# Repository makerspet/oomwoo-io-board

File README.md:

<div align="center">

# OOMWOO I/O Board

*Open-source robot vacuum you build yourself.*

Raspberry Pi CM4/CM5 socket · STM32G473 MCU · Motor drivers · Sensors · 2x MIPI cameras · 4S charging · KiCad

</div>

Part of [OOMWOO open-source robot vacuum](https://github.com/makerspet/oomwoo) project.

Get [MCU firmware](https://github.com/makerspet/oomwoo-io-firmware/).

## Architecture notes

Consumer vacuums typically split compute into CPU and MCU. The MCU ([real examples](https://robotinfo.dev/)) controls
- all motors - driving wheels, suction fan, side brushes, mop motors, mop lift servos, pump and so on
- all sensors except below - IR cliff, IR side proximity, IR docking, wheel drop, bumper (IR or micro-switches), motor encoders, ultrasonic carpet sensor
- all push buttons
- 2D LiDAR motor RPM
- power - battery charging, motors power on/off
- all safety sensors - overcurrent for all motors (cheap vacuums ignore overcurrent sensing)

I/O board also provides audio encoders/decoders, amp, speaker (connector), mics (if any).

CPU receives
- 2D LiDAR data over serial port
- IMU (sometimes IMU gets forwarded via MCU) over SPI/I2C
- cameras (2x MIPI for visual obstacle avoidance)

MCU (and CPU) are usually always active. This allows the user to start cleaning at any time (especially via app remotely). Exceptions:
- no power (battery dead and no dock power)
- user explicitly shut down the vacuum by long-pressing the power button

The MCU's overarching constraint is to ensure robot safety. This is necessary to pass CE mark tests. Here is how MCU ensures safety:
- MCU firmware uses FreeRTOS or similar, static memory allocation, watchdog, guaranteed reaction time
- MCU acts as watchdog for CPU, resets CPU if CPU becomes unresponsive
- MCU connects to CPU over serial using a custom serial protocol ([concrete example](https://github.com/codetiger/VacuumRobot)). No micro-ROS to reduce dependencies, prevent bugs from updated 3rd party libraries slipping into safety-critical MCU firmware.
- MCU shuts down some (or all) motors when MCU detects overcurrent (brush stuck)
- MCU shuts down all motors (including power to all motors) when CPU becomes unresponsive (to prevent CPU sending garbage commands to MCU)
- MCU monitors battery charging, shuts it down when needed (battery too hot)
- MCU stops driving wheel motors when bumper sensors activate
- MCU tests motors, sensors
- MCU does not depend on CPU
- MCU toggles watchdog GPIO; otherwise an external-to-MCU circuit shuts down motor power

Consumer vacuums place CPU and MCU on the same PCB board. Since OOMWOO has to be hackable, it seems best to separate I/O from the compute. Therefore, this I/O board needs to have
- MCU and programming header
  - likely STM32G070RBT6 because it has 56 GPIOs, 16 ADC channels, costs $1 at JLCPCB, has LQFP package for easy PCBA - a rare combination
  - see tentative [I/O board spec](https://github.com/makerspet/oomwoo-io-board/blob/main/docs/SPEC.md)
- all vacuum motor drivers (with connectors), driven by the MCU
  - cliff, side proximity, docking, bumper, carpet, water tank full/empty, dust bin present, motor overcurrent, motor encoders
- MCU connected to all sensors (except those handled by CPU like LiDAR serial, MIPI cameras I/O, IMU); sensor connectors
- control circuit for 2D LiDAR's motor (controlled by MCU)
- battery charging, power management (motors power on/off, charging on/off, power shut down), power for CPU compute module (see below)
- push buttons (home, power, etc.) and UI LEDs
- dock connector (dock power, sense dock present)
- USB power for charging; USB for serial shell, etc.
- audio encoder/decoder, audio amp, mics (if any)
- SD card for hacking, cheap large storage
- connect IMU FSYNC to MCU to synchronize MCU timestamps with IMU data streaming to CPU

Consumer vacuums usually don't have a CPU fan/heatsink because the vacuum's suction fan can (indirectly) cool the CPU/MCU PCB. Therefore, no CPU fan on this I/O board.

As far as compute - currently it seems best to use a Raspberry Pi CM4/CM5 compute module. Why?
- CM4/CM5 modules cost a bit less than a full Raspberry Pi 4/5
- CM4/CM5 have lower profile/height vs a full Raspberry Pi 4/5, important to keep vacuum cleaner slim
- there are plenty of 3rd party compute modules pin-compatible with CM4/CM5, making the compute swappable, hackable
  - 3rd party compute modules with NPUs are especially interesting because we need NPU for real-time camera-based obstacle detection

Compute module headers should expose
- 2x MIPI camera I/O
- 1x serial for CPU-MCU comms
- 1x serial for CPU-LiDAR comms
- 1x SPI (or I2C) for CPU-IMU comms
- audio (digital?) I/O
- power from I/O board to CM
- a few TBD GPIOs
  - MCU GPIO to reset CPU

This board should be designed using an open-source PCB tool (KiCad seems like a good choice).

## License

[Apache License 2.0](LICENSE).

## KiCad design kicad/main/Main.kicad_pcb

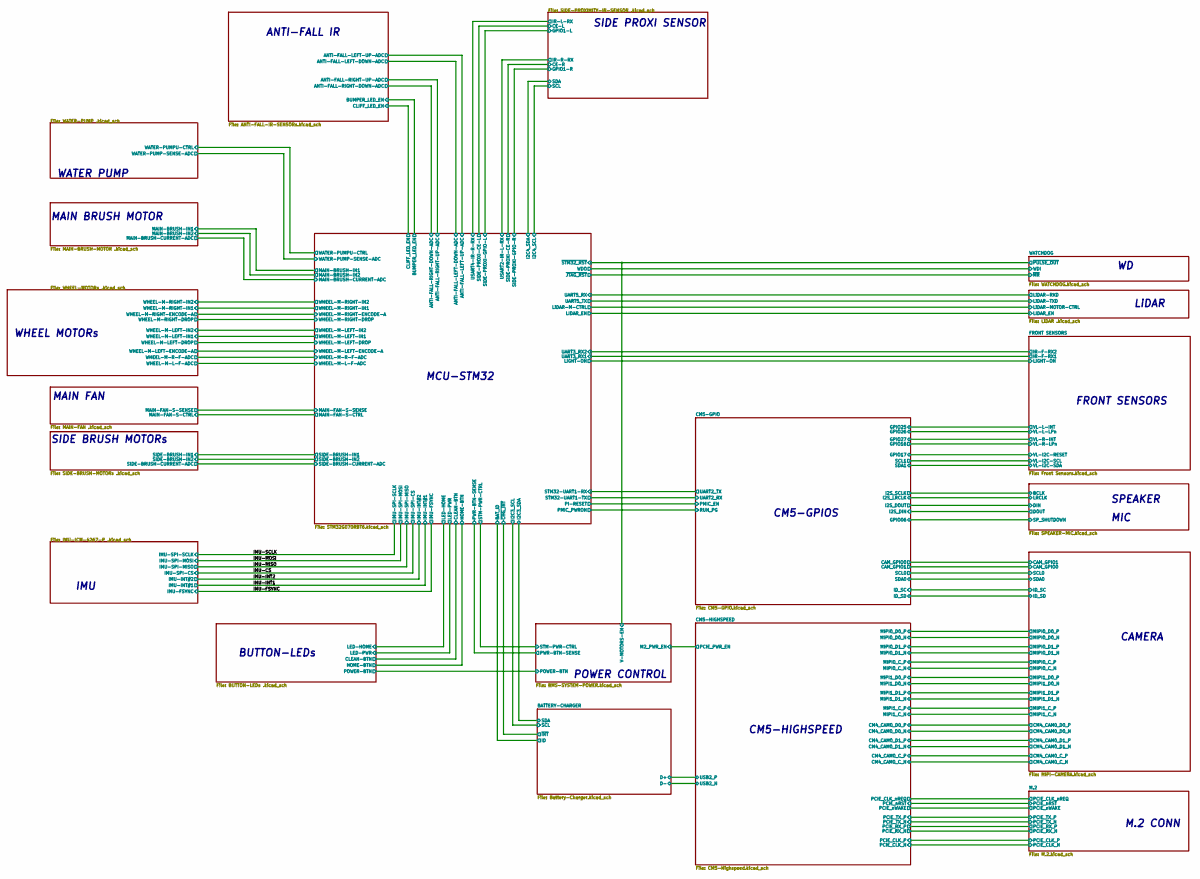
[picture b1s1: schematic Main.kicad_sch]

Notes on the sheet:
IMU
ANTI-FALL IR
WATER PUMP
FRONT SENSORS
M.2 CONN
CAMERA
MAIN FAN
BUTTON-LEDs
SIDE PROXI SENSOR
MCU-STM32
CM5-HIGHSPEED
SPEAKER
POWER CONTROL
WHEEL MOTORs
LiDAR
SIDE BRUSH MOTORs
MAIN BRUSH MOTOR
CM5-GPIOS
MIC

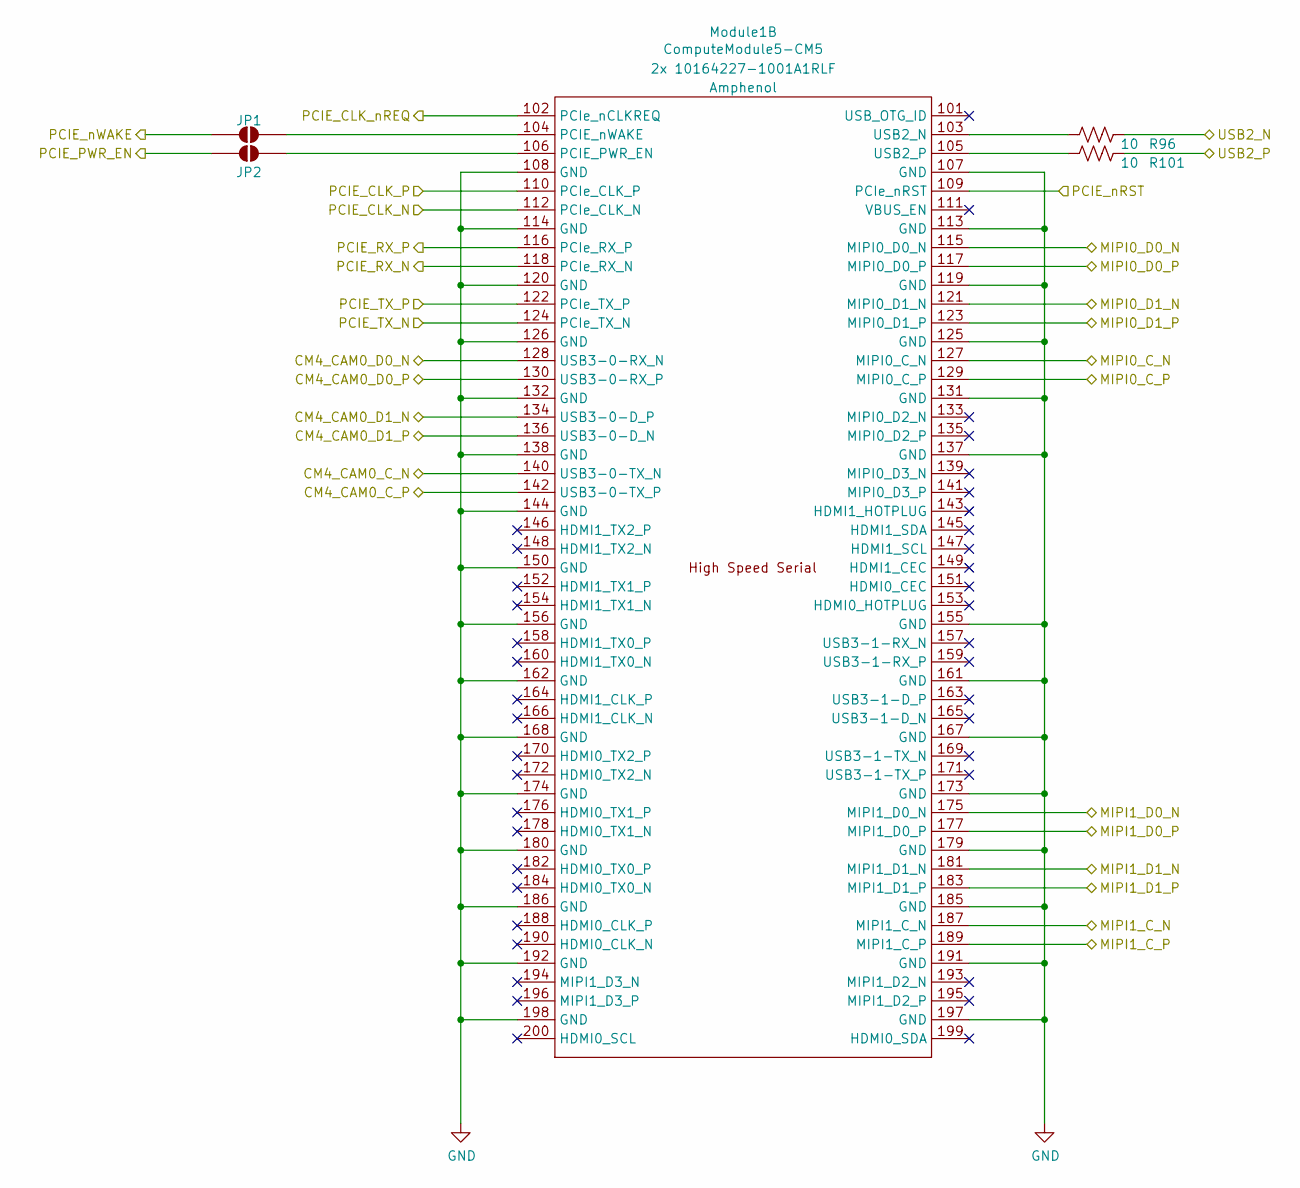
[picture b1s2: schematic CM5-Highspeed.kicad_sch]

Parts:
JP1, JP2: SolderJumper-2_P1.3mm_Open_RoundedPad1.0x1.5mm
Module1: ComputeModule5-CM5; Raspberry-Pi-5-Compute-Module; Part Description 100 Position Connector Receptacle, Cent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; LCSC 2X C6932320
R96, R101: 10; R_0603_1608Metric

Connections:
/BATTERY-CHARGER/D+: R101.2; also elsewhere on the board
/BATTERY-CHARGER/D-: R96.2; also elsewhere on the board
/CAMERA/CM4_CAM0_C_N: Module1.140 (USB3-0-TX_N); also elsewhere on the board
/CAMERA/CM4_CAM0_C_P: Module1.142 (USB3-0-TX_P); also elsewhere on the board
/CAMERA/CM4_CAM0_D0_N: Module1.128 (USB3-0-RX_N); also elsewhere on the board
/CAMERA/CM4_CAM0_D0_P: Module1.130 (USB3-0-RX_P); also elsewhere on the board
/CAMERA/CM4_CAM0_D1_N: Module1.134 (USB3-0-D_P); also elsewhere on the board
/CAMERA/CM4_CAM0_D1_P: Module1.136 (USB3-0-D_N); also elsewhere on the board
/CAMERA/MIPI0_C_N: Module1.127 (MIPI0_C_N); also elsewhere on the board
/CAMERA/MIPI0_C_P: Module1.129 (MIPI0_C_P); also elsewhere on the board
/CAMERA/MIPI0_D0_N: Module1.115 (MIPI0_D0_N); also elsewhere on the board
/CAMERA/MIPI0_D0_P: Module1.117 (MIPI0_D0_P); also elsewhere on the board
/CAMERA/MIPI0_D1_N: Module1.121 (MIPI0_D1_N); also elsewhere on the board
/CAMERA/MIPI0_D1_P: Module1.123 (MIPI0_D1_P); also elsewhere on the board
/CAMERA/MIPI1_C_N: Module1.187 (MIPI1_C_N); also elsewhere on the board
/CAMERA/MIPI1_C_P: Module1.189 (MIPI1_C_P); also elsewhere on the board
/CAMERA/MIPI1_D0_N: Module1.175 (MIPI1_D0_N); also elsewhere on the board
/CAMERA/MIPI1_D0_P: Module1.177 (MIPI1_D0_P); also elsewhere on the board
/CAMERA/MIPI1_D1_N: Module1.181 (MIPI1_D1_N); also elsewhere on the board
/CAMERA/MIPI1_D1_P: Module1.183 (MIPI1_D1_P); also elsewhere on the board
/CM5-HIGHSPEED/PCIE_CLK_N: Module1.112 (PCIe_CLK_N); also elsewhere on the board
/CM5-HIGHSPEED/PCIE_CLK_P: Module1.110 (PCIe_CLK_P); also elsewhere on the board
/CM5-HIGHSPEED/PCIE_CLK_nREQ: Module1.102 (PCIe_nCLKREQ); also elsewhere on the board
/CM5-HIGHSPEED/PCIE_PWR_EN: JP2.1 (A); also elsewhere on the board
/CM5-HIGHSPEED/PCIE_RX_N: Module1.118 (PCIe_RX_N); also elsewhere on the board
/CM5-HIGHSPEED/PCIE_RX_P: Module1.116 (PCIe_RX_P); also elsewhere on the board
/CM5-HIGHSPEED/PCIE_TX_N: Module1.124 (PCIe_TX_N); also elsewhere on the board
/CM5-HIGHSPEED/PCIE_TX_P: Module1.122 (PCIe_TX_P); also elsewhere on the board
/CM5-HIGHSPEED/PCIE_nRST: Module1.109 (PCIe_nRST); also elsewhere on the board
/CM5-HIGHSPEED/PCIE_nWAKE: JP1.1 (A); also elsewhere on the board
GND: Module1.107 (GND), Module1.108 (GND), Module1.113 (GND), Module1.114 (GND), Module1.119 (GND), Module1.120 (GND), Module1.125 (GND), Module1.126 (GND), Module1.131 (GND), Module1.132 (GND), Module1.137 (GND), Module1.138 (GND), Module1.144 (GND), Module1.150 (GND), Module1.155 (GND), Module1.156 (GND), Module1.161 (GND), Module1.162 (GND), Module1.167 (GND), Module1.168 (GND), Module1.173 (GND), Module1.174 (GND), Module1.179 (GND), Module1.180 (GND), Module1.185 (GND), Module1.186 (GND), Module1.191 (GND), Module1.192 (GND), Module1.197 (GND), Module1.198 (GND); also elsewhere on the board
unnamed: JP1.2 (B), Module1.104 (PCIE_nWAKE)
unnamed: JP2.2 (B), Module1.106 (PCIE_PWR_EN)
unnamed: Module1.103 (USB2_N), R96.1
unnamed: Module1.105 (USB2_P), R101.1

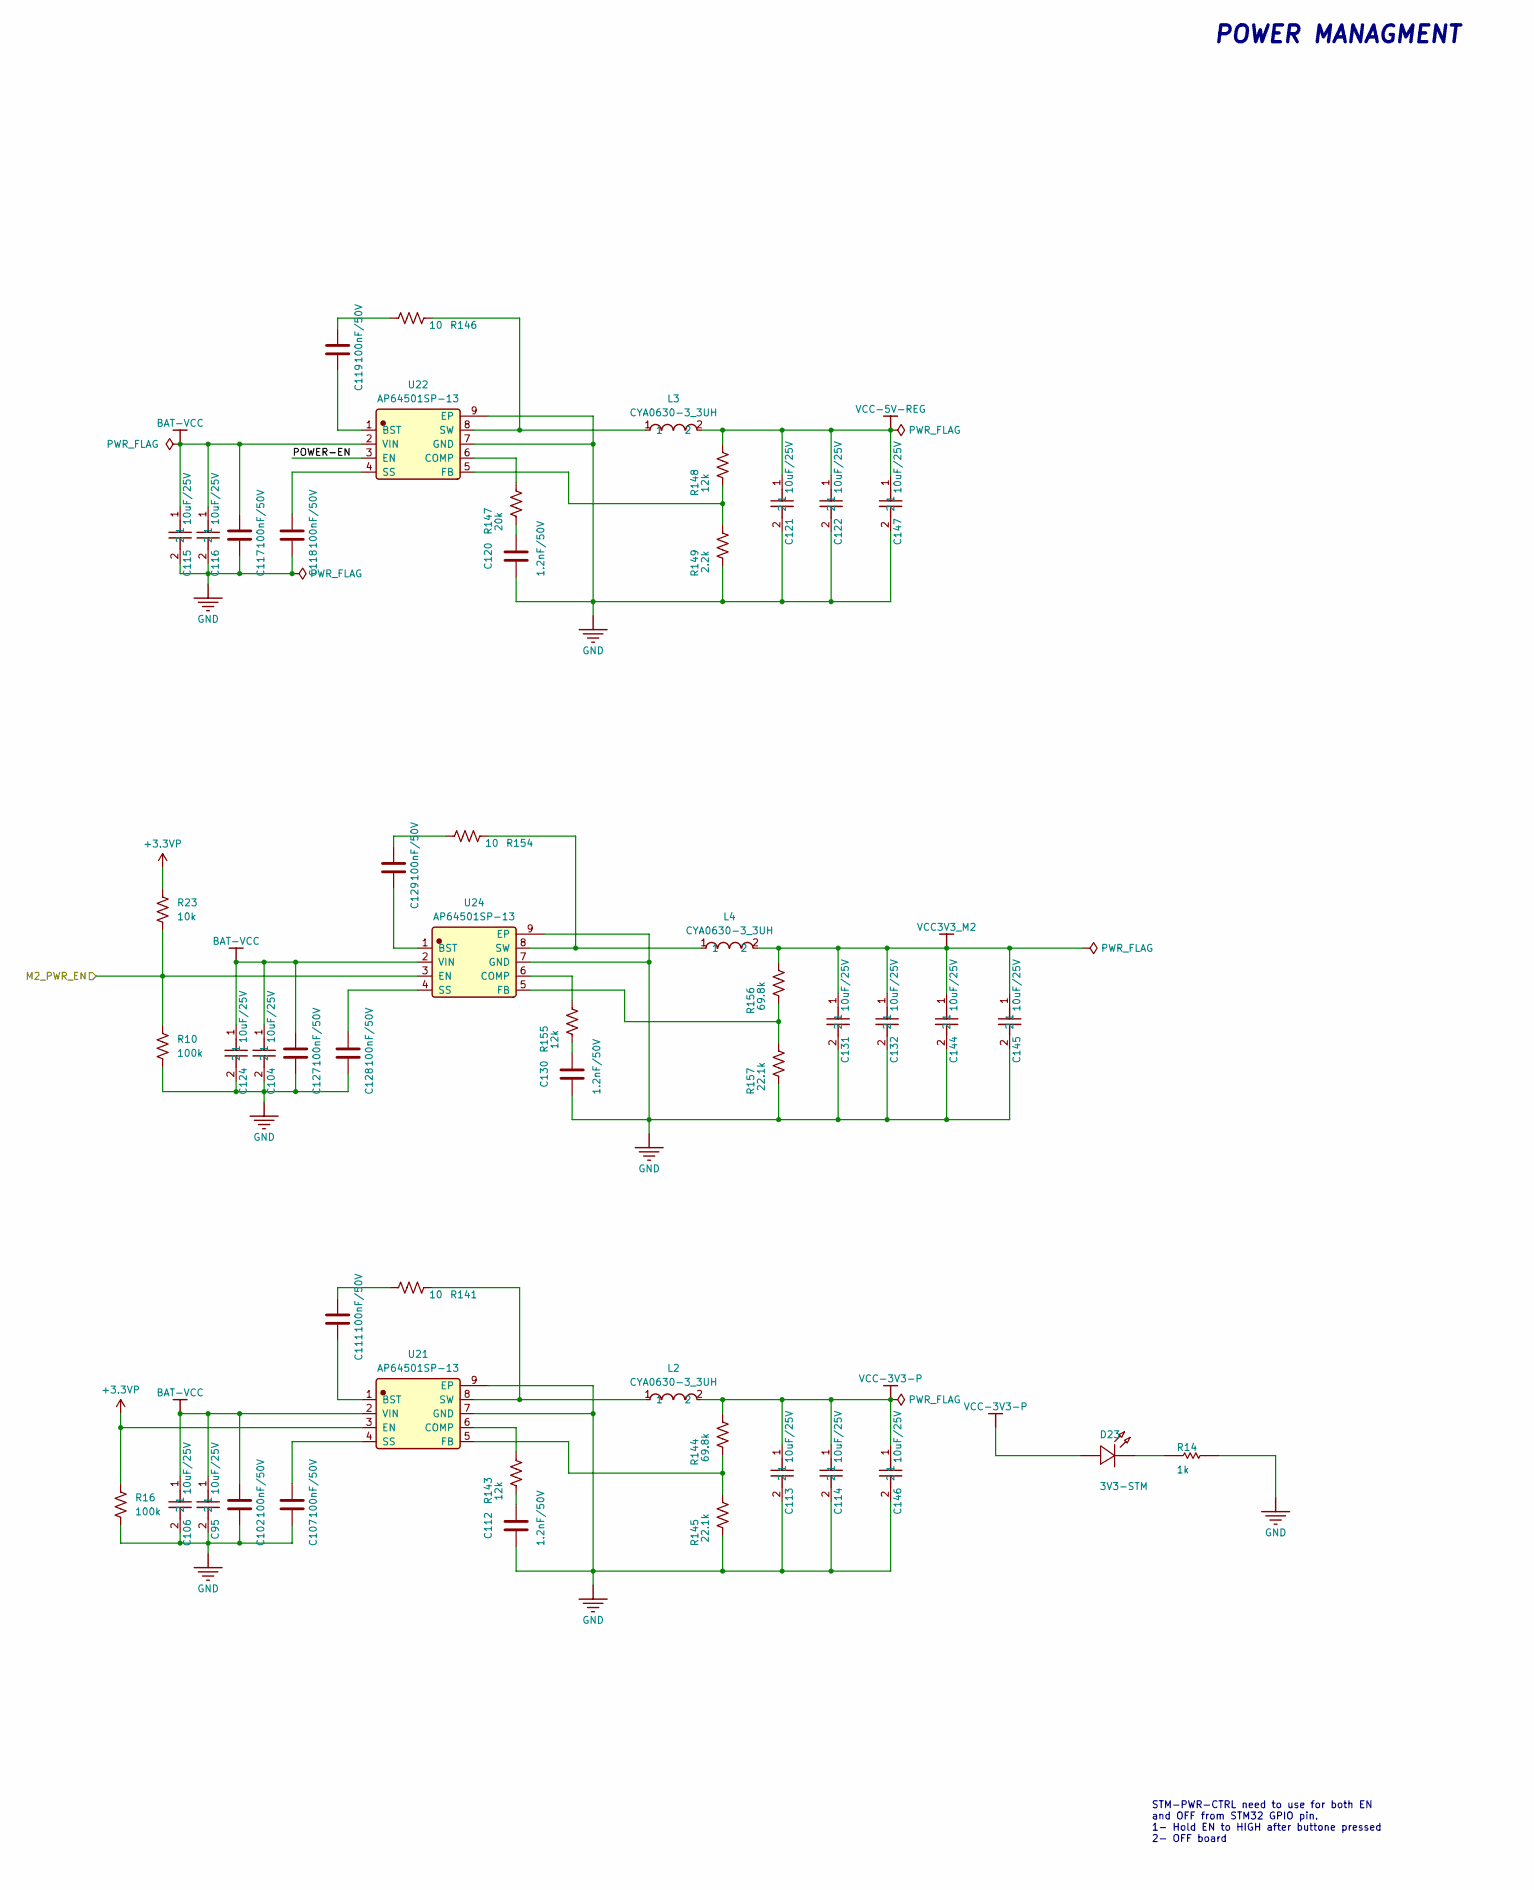
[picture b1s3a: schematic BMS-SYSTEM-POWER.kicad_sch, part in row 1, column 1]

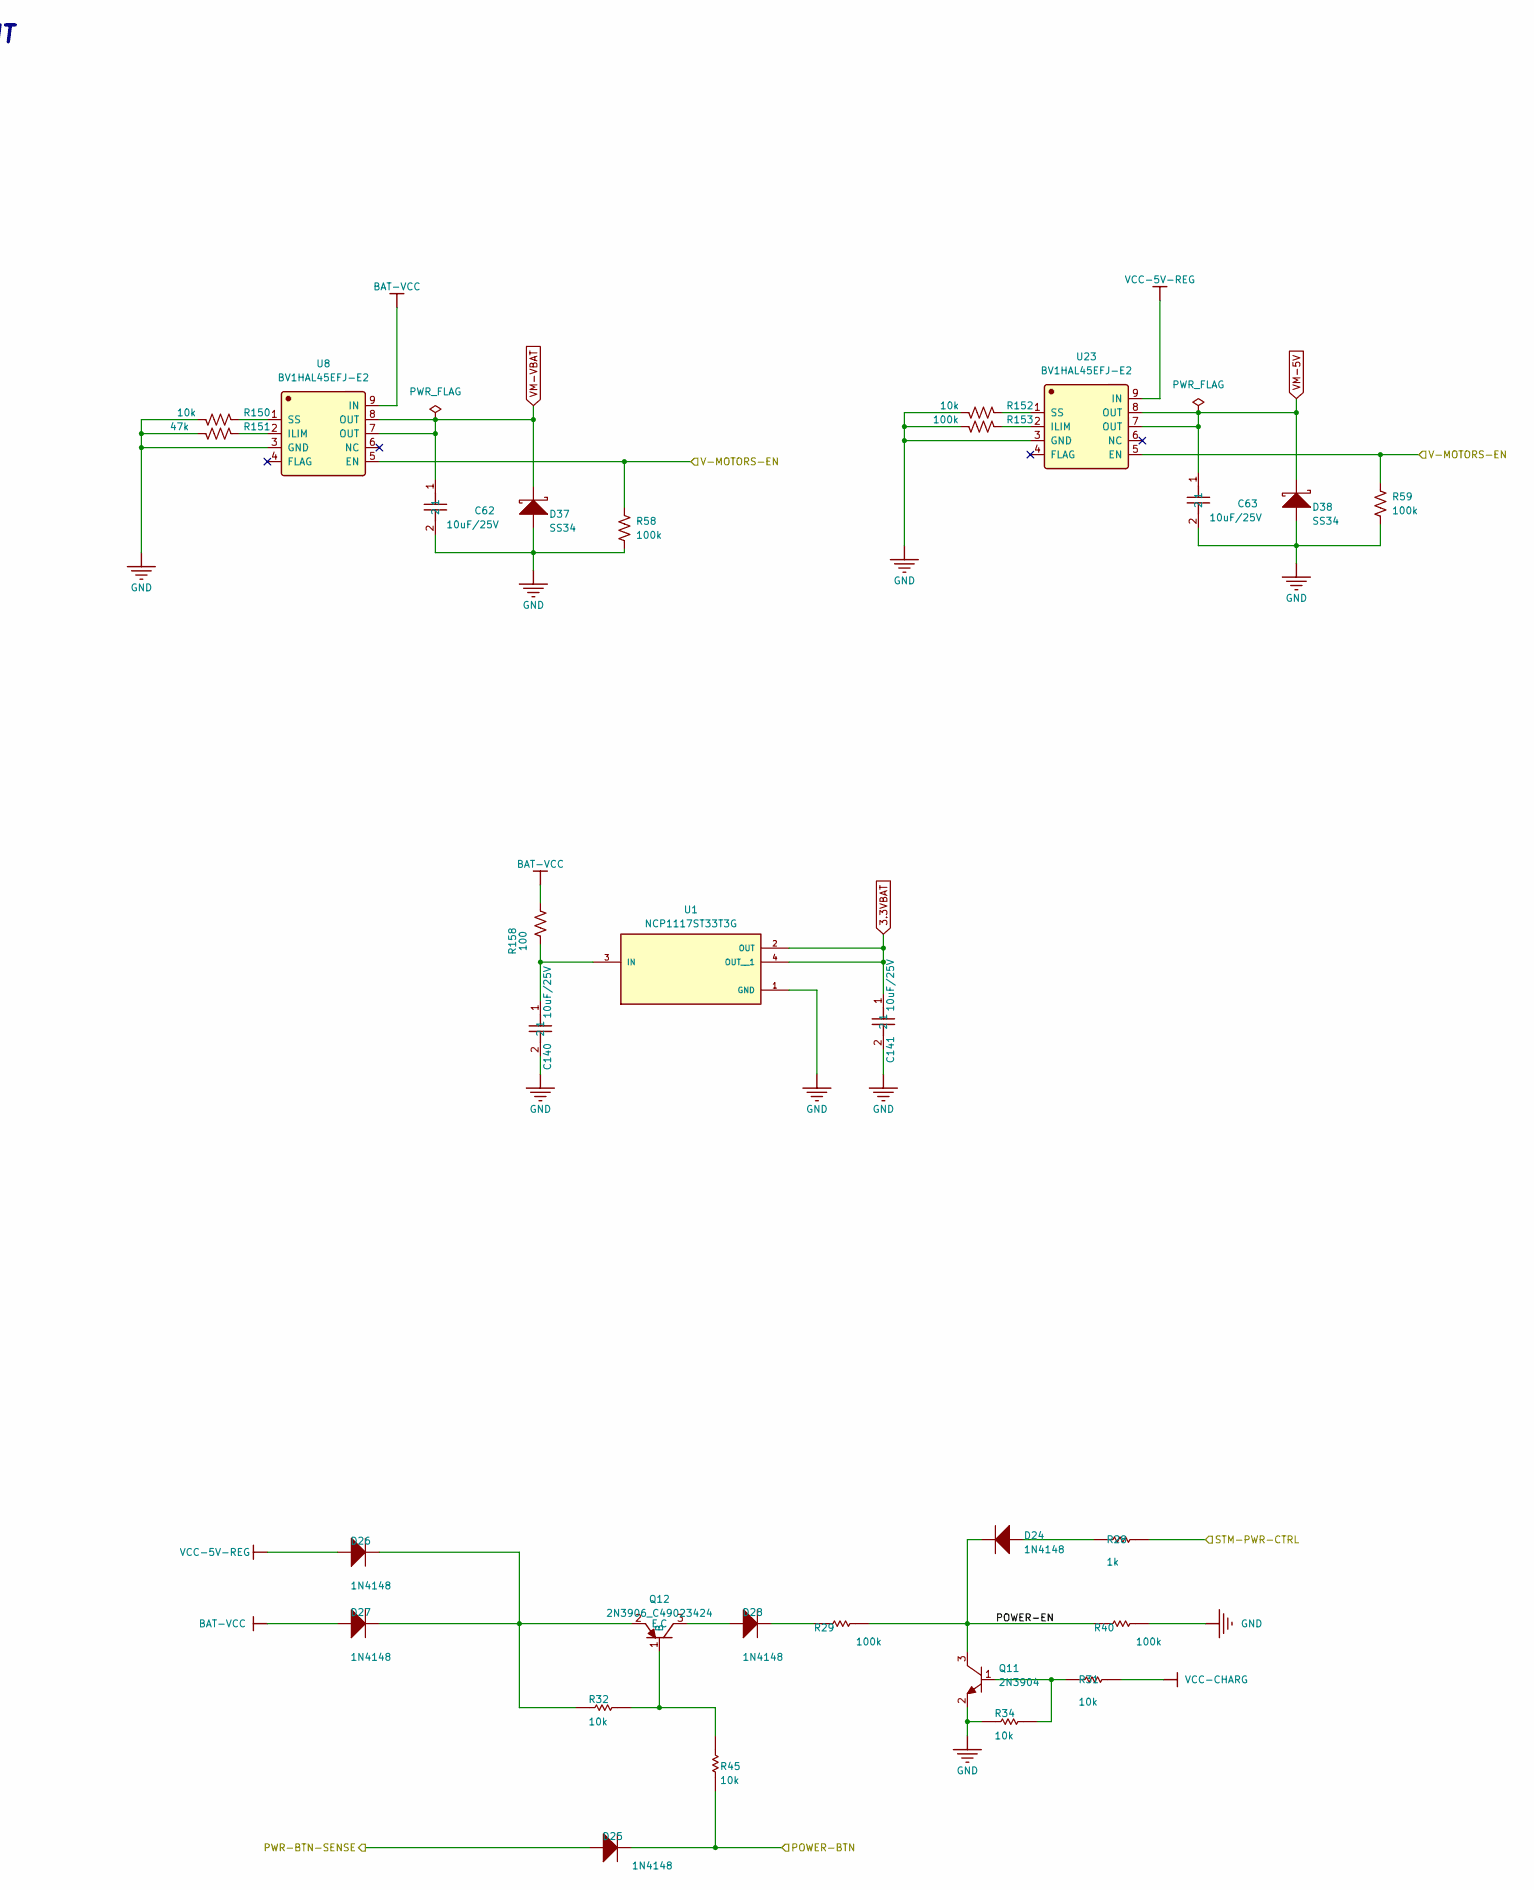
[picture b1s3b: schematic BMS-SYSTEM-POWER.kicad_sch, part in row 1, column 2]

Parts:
C62, C63, C95, C104, C106, C113, C114, C115, C116, C121, C122, C124, C131, C132, C140, C141, C144, C145, C146, C147: 10uF/25V; C_0603_1608Metric; LCSC C96446
C102, C107, C111, C117, C118, C119, C127, C128, C129: 100nF/50V; C_0603_1608Metric; Manufacturer_Part_Number CL10B104KB8NNNC; LCSC C1591
C112, C120, C130: 1.2nF/50V; C_0603_1608Metric; Manufacturer_Part_Number CL10B104KB8NNNC; LCSC C1590
D23: 3V3-STM; LED0603-B; VOLTAGERATE *; MANUFACTURINGPARTNUMBER *; LCSC C19171394
D24, D25, D26, D27, D28: 1N4148; SOD123; VOLTAGERATE *; MANUFACTURINGPARTNUMBER *; LCSC C917030
D37, D38: SS34; D_SMA; VOLTAGERATE *; MANUFACTURINGPARTNUMBER *; LCSC C22448055
L2, L3, L4: CYA0630-3_3UH; Manufacturer Part CYA0630-3.3UH; LCSC C5189747
Q11: 2N3904; SOT23-3D; VOLTAGERATE *; MANUFACTURINGPARTNUMBER *; LCSC C50176433
Q12: 2N3906_C49023424; Manufacturer Part 2N3906; LCSC C49023424
R10, R16, R58, R59, R153: 100k; R_0603_1608Metric
R14, R28: 1k; R_0603_1608Metric; VOLTAGERATE *; MANUFACTURINGPARTNUMBER *
R23, R150, R152: 10k; R_0603_1608Metric
R29, R40: 100k; R_0603_1608Metric; VOLTAGERATE *; MANUFACTURINGPARTNUMBER *
R31, R32, R34, R45: 10k; R_0603_1608Metric; VOLTAGERATE *; MANUFACTURINGPARTNUMBER *
R141, R146, R154: 10; R_0603_1608Metric
R143, R148, R155: 12k; R_0603_1608Metric
R144, R156: 69.8k; R_0603_1608Metric
R145, R157: 22.1k; R_0603_1608Metric
R147: 20k; R_0603_1608Metric
R149: 2.2k; R_0603_1608Metric
R151: 47k; R_0603_1608Metric
R158: 100; R_0805_2012Metric
U1: NCP1117ST33T3G; SOT230P700X180-4N; LCSC C26537
U8, U23: BV1HAL45EFJ-E2; Manufacturer Part BV1HAL45EFJ-E2; LCSC C3229246
U21, U22, U24: AP64501SP-13; Manufacturer Part AP64501SP-13; LCSC C2071517

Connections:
3.3VBAT: C141.1, U1.2 (OUT), U1.4 (OUT__1); also elsewhere on the board
+3.3VP: R16.1, R23.1, U21.3 (EN); also elsewhere on the board
/BUTTON-LED/POWER-BTN: D25.2 (K), R45.1; also elsewhere on the board
/CM5-HIGHSPEED/PCIE_PWR_EN: R10.1, R23.2, U24.3 (EN); also elsewhere on the board
/MCU-STM32/PWR-BTN-SENSE: D25.1 (A); also elsewhere on the board
/MCU-STM32/STM-PWR-CTRL: R28.2; also elsewhere on the board
/MCU-STM32/~STM32_RST: R58.1, R59.1, U8.5 (EN), U23.5 (EN); also elsewhere on the board
/POWER/POWER-EN: D24.2 (K), Q11.3 (C), R29.2, R40.1, U22.3 (EN)
BAT-VCC: C95.1, C102.1, C104.1, C106.1, C115.1, C116.1, C117.1, C124.1, C127.1, D27.1 (A), R158.2, U8.9 (IN), U21.2 (VIN), U22.2 (VIN), U24.2 (VIN); also elsewhere on the board
GND: C62.2, C63.2, C95.2, C102.2, C104.2, C106.2, C107.2, C112.2, C113.2, C114.2, C115.2, C116.2, C117.2, C118.2, C120.2, C121.2, C122.2, C124.2, C127.2, C128.2, C130.2, C131.2, C132.2, C140.2, C141.2, C144.2, C145.2, C146.2, C147.2, D37.1 (A), D38.1 (A), Q11.2 (E), R10.2, R14.1, R16.2, R34.2, R40.2, R58.2, R59.2, R145.1, R149.1, R150.1, R151.1, R152.1, R153.1, R157.1, U1.1 (GND), U8.3 (GND), U21.7 (GND), U21.9 (EP), U22.7 (GND), U22.9 (EP), U23.3 (GND), U24.7 (GND), U24.9 (EP); also elsewhere on the board
unnamed: C111.1, R141.1
unnamed: C112.1, R143.1
unnamed: C119.1, R146.1
unnamed: C120.1, R147.1
unnamed: C129.1, R154.1
unnamed: C130.1, R155.1
unnamed: D23.2, R14.2
unnamed: D24.1 (A), R28.1
unnamed: D26.2 (K), D27.2 (K), Q12.2 (E), R32.2
unnamed: D28.1 (A), Q12.3 (C)
unnamed: D28.2 (K), R29.1
unnamed: Q11.1 (B), R31.1, R34.1
unnamed: Q12.1 (B), R32.1, R45.2
unnamed: C140.1, R158.1, U1.3 (IN)
unnamed: R151.2, U8.2 (ILIM)
unnamed: R150.2, U8.1 (SS)
unnamed: C111.2, U21.1 (BST)
unnamed: R143.2, U21.6 (COMP)
unnamed: R144.1, R145.2, U21.5 (FB)
unnamed: C107.1, U21.4 (SS)
unnamed: L2.1, R141.2, U21.8 (SW)
unnamed: C119.2, U22.1 (BST)
unnamed: R147.2, U22.6 (COMP)
unnamed: R148.1, R149.2, U22.5 (FB)
unnamed: C118.1, U22.4 (SS)
unnamed: L3.1, R146.2, U22.8 (SW)
unnamed: R153.2, U23.2 (ILIM)
unnamed: R152.2, U23.1 (SS)
unnamed: C129.2, U24.1 (BST)
unnamed: R155.2, U24.6 (COMP)
unnamed: R156.1, R157.2, U24.5 (FB)
unnamed: C128.1, U24.4 (SS)
unnamed: L4.1, R154.2, U24.8 (SW)
VCC3V3_M2: C131.1, C132.1, C144.1, C145.1, L4.2, R156.2; also elsewhere on the board
VCC-3V3-P: C113.1, C114.1, C146.1, D23.1, L2.2, R144.2; also elsewhere on the board
VCC-5V-REG: C121.1, C122.1, C147.1, D26.1 (A), L3.2, R148.2, U23.9 (IN); also elsewhere on the board
VCC-CHARG: R31.2; also elsewhere on the board
VM-5V: C63.1, D38.2 (K), U23.7 (OUT), U23.8 (OUT); also elsewhere on the board
VM-VBAT: C62.1, D37.2 (K), U8.7 (OUT), U8.8 (OUT); also elsewhere on the board

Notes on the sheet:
POWER MANAGMENT
STM-PWR-CTRL need to use for both EN and OFF from STM32 GPIO pin. 1- Hold EN to HIGH after buttone pressed 2- OFF board

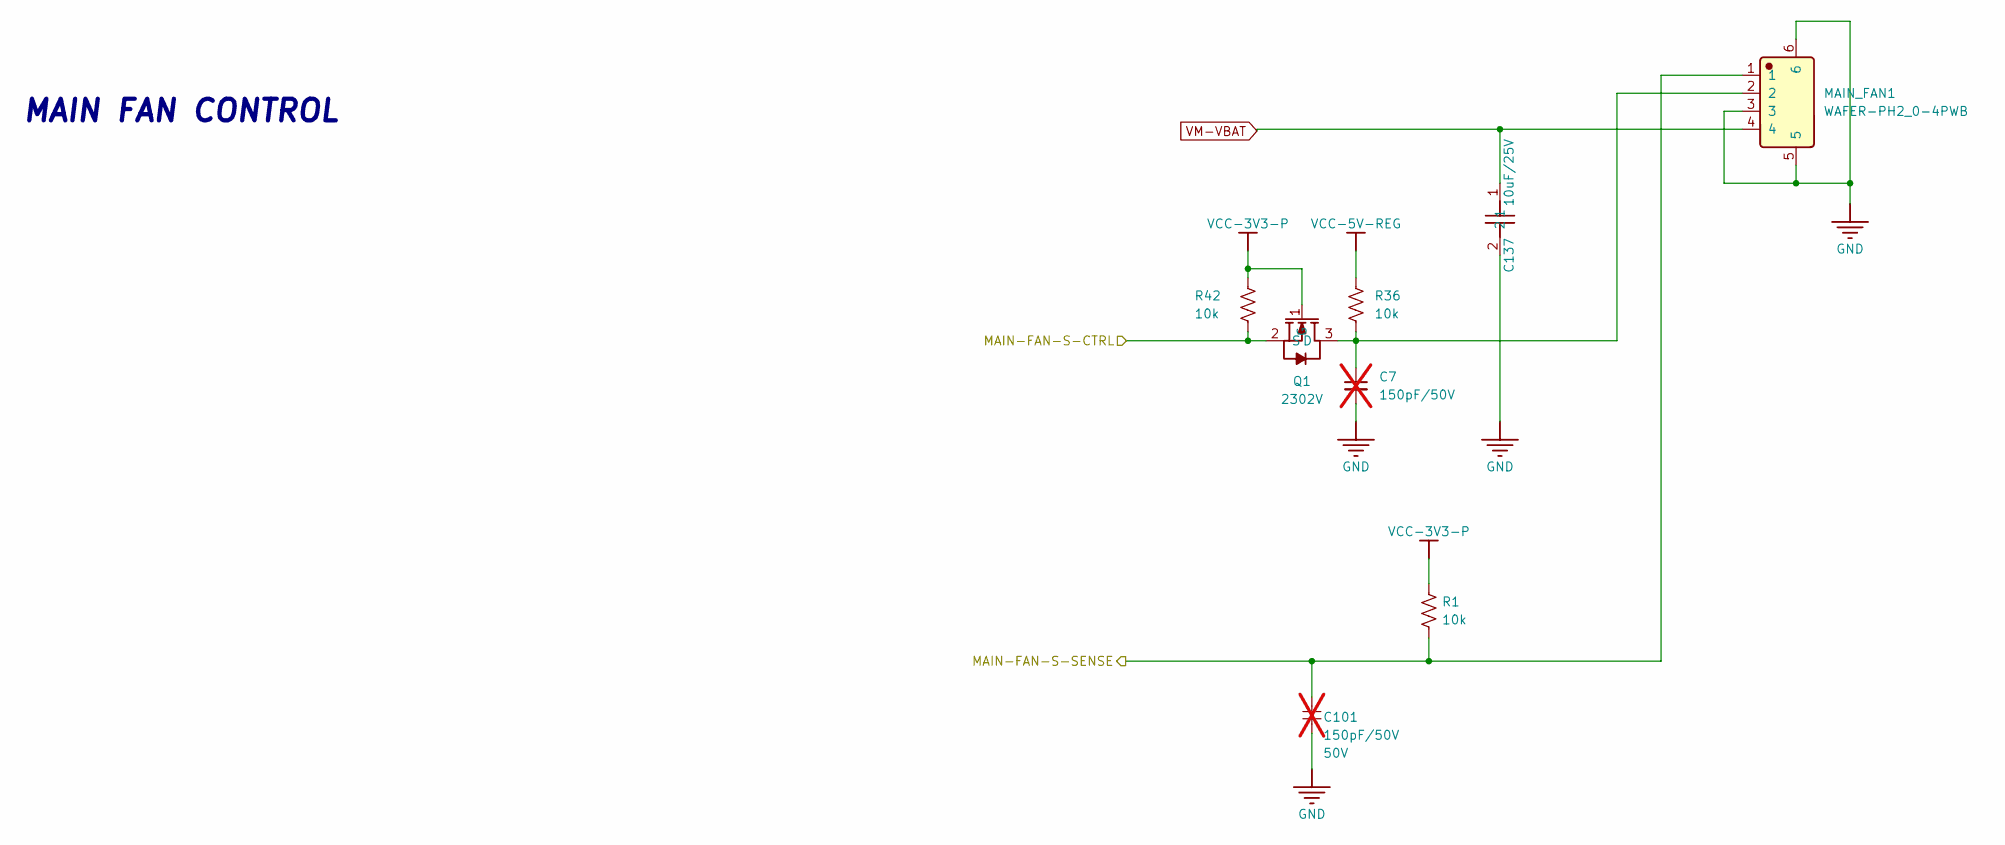
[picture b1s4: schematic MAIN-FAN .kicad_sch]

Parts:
C7: 150pF/50V; C_0603_1608Metric; not fitted
C101: 150pF/50V; C_0603_1608Metric; VOLTAGERATE 50V; MANUFACTURINGPARTNUMBER *; not fitted
C137: 10uF/25V; C_0603_1608Metric; LCSC C96446
MAIN_FAN1: WAFER-PH2_0-4PWB; Manufacturer Part WAFER-PH2.0-4PWB; LCSC C3029442
Q1: 2302V; Manufacturer Part 2302V; LCSC C7431443
R1, R36, R42: 10k; R_0603_1608Metric

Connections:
/MAIN-FAN/MAIN-FAN-S-CTRL: Q1.2 (S), R42.2; also elsewhere on the board
/MAIN-FAN/MAIN-FAN-S-SENSE: C101.1, MAIN_FAN1.1, R1.2; also elsewhere on the board
GND: C7.2, C101.2, C137.2, MAIN_FAN1.3, MAIN_FAN1.5, MAIN_FAN1.6; also elsewhere on the board
unnamed: C7.1, MAIN_FAN1.2, Q1.3 (D), R36.2
VCC-3V3-P: Q1.1 (G), R1.1, R42.1; also elsewhere on the board
VCC-5V-REG: R36.1; also elsewhere on the board
VM-VBAT: C137.1, MAIN_FAN1.4; also elsewhere on the board

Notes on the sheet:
MAIN FAN CONTROL

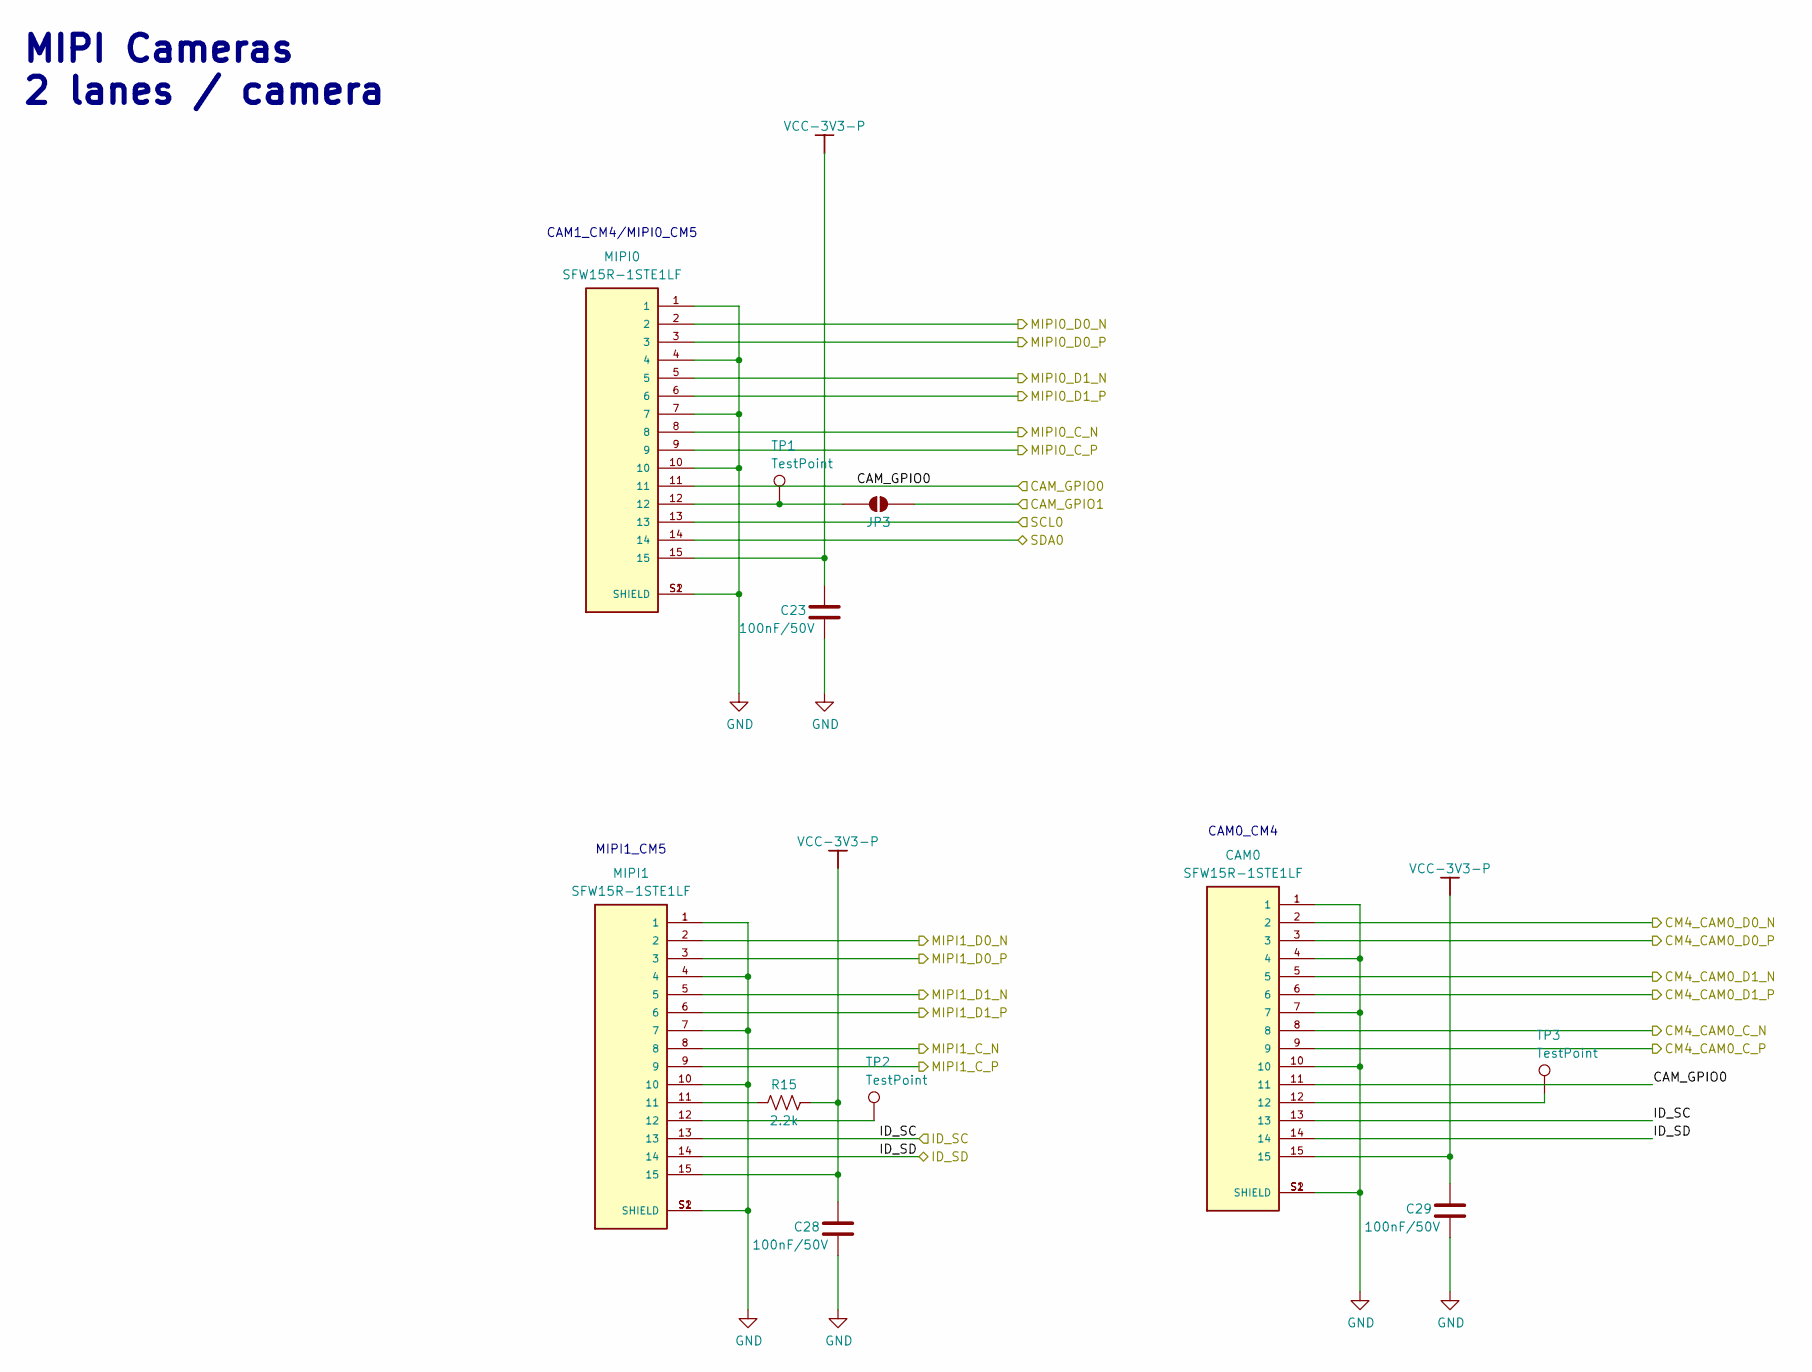
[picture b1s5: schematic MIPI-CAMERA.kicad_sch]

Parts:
C23, C28, C29: 100nF/50V; C_0603_1608Metric; LCSC C1591
CAM0: SFW15R-1STE1LF; AMPHENOL_SFW15R-1STE1LF; PARTREV AC; LCSC C3168538
JP3: SolderJumper-2_P1.3mm_Open_RoundedPad1.0x1.5mm
MIPI0, MIPI1: SFW15R-1STE1LF; AMPHENOL_SFW15R-1STE1LF; PARTREV AC; LCSC C3168538
R15: 2.2k; R_0603_1608Metric
TP1, TP2, TP3: TestPoint; TestPoint_Pad_D2.0mm

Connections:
/CAMERA/CAM_GPIO0: CAM0.11, MIPI0.11; also elsewhere on the board
/CAMERA/CAM_GPIO1: JP3.2 (B); also elsewhere on the board
/CAMERA/CM4_CAM0_C_N: CAM0.8; also elsewhere on the board
/CAMERA/CM4_CAM0_C_P: CAM0.9; also elsewhere on the board
/CAMERA/CM4_CAM0_D0_N: CAM0.2; also elsewhere on the board
/CAMERA/CM4_CAM0_D0_P: CAM0.3; also elsewhere on the board
/CAMERA/CM4_CAM0_D1_N: CAM0.5; also elsewhere on the board
/CAMERA/CM4_CAM0_D1_P: CAM0.6; also elsewhere on the board
/CAMERA/ID_SC: CAM0.13, MIPI1.13; also elsewhere on the board
/CAMERA/ID_SD: CAM0.14, MIPI1.14; also elsewhere on the board
/CAMERA/MIPI0_C_N: MIPI0.8; also elsewhere on the board
/CAMERA/MIPI0_C_P: MIPI0.9; also elsewhere on the board
/CAMERA/MIPI0_D0_N: MIPI0.2; also elsewhere on the board
/CAMERA/MIPI0_D0_P: MIPI0.3; also elsewhere on the board
/CAMERA/MIPI0_D1_N: MIPI0.5; also elsewhere on the board
/CAMERA/MIPI0_D1_P: MIPI0.6; also elsewhere on the board
/CAMERA/MIPI1_C_N: MIPI1.8; also elsewhere on the board
/CAMERA/MIPI1_C_P: MIPI1.9; also elsewhere on the board
/CAMERA/MIPI1_D0_N: MIPI1.2; also elsewhere on the board
/CAMERA/MIPI1_D0_P: MIPI1.3; also elsewhere on the board
/CAMERA/MIPI1_D1_N: MIPI1.5; also elsewhere on the board
/CAMERA/MIPI1_D1_P: MIPI1.6; also elsewhere on the board
/CAMERA/SCL0: MIPI0.13; also elsewhere on the board
/CAMERA/SDA0: MIPI0.14; also elsewhere on the board
GND: C23.2, C28.2, C29.2, CAM0.1, CAM0.4, CAM0.7, CAM0.10, CAM0.S1 (SHIELD), CAM0.S2 (SHIELD), MIPI0.1, MIPI0.4, MIPI0.7, MIPI0.10, MIPI0.S1 (SHIELD), MIPI0.S2 (SHIELD), MIPI1.1, MIPI1.4, MIPI1.7, MIPI1.10, MIPI1.S1 (SHIELD), MIPI1.S2 (SHIELD); also elsewhere on the board
unnamed: CAM0.12, TP3.1 (1_1)
unnamed: JP3.1 (A), MIPI0.12, TP1.1 (1_1)
unnamed: MIPI1.11, R15.1
unnamed: MIPI1.12, TP2.1 (1_1)
VCC-3V3-P: C23.1, C28.1, C29.1, CAM0.15, MIPI0.15, MIPI1.15, R15.2; also elsewhere on the board

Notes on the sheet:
CAM1_CM4/MIPI0_CM5
CAM0_CM4
MIPI1_CM5
MIPI Cameras 2 lanes / camera

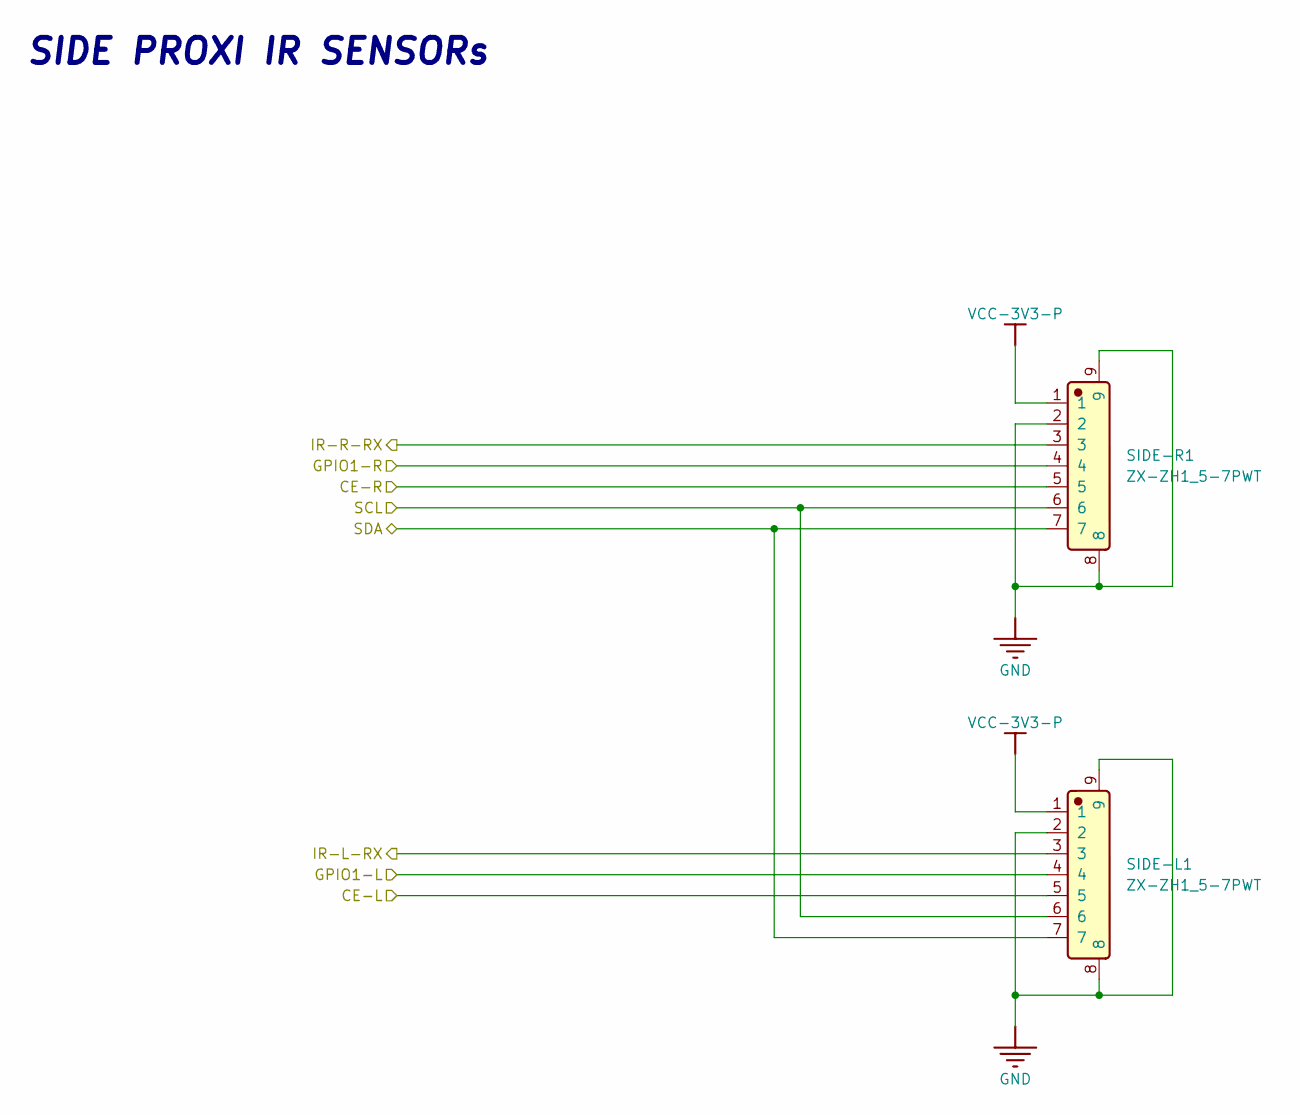
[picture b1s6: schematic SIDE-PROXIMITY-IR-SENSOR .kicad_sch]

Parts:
SIDE-L1: ZX-ZH1_5-7PWT; Manufacturer Part ZX-ZH1.5-7PWT; LCSC C19272410
SIDE-R1: ZX-ZH1_5-7PWT; Manufacturer Part ZX-ZH1.5-7PWT; LCSC C19272410

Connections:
/MCU-STM32/I2C4_SCL: SIDE-L1.6, SIDE-R1.6; also elsewhere on the board
/MCU-STM32/I2C4_SDA: SIDE-L1.7, SIDE-R1.7; also elsewhere on the board
/MCU-STM32/SIDE-PROXI-CE-L: SIDE-L1.5; also elsewhere on the board
/MCU-STM32/SIDE-PROXI-CE-R: SIDE-R1.5; also elsewhere on the board
/MCU-STM32/SIDE-PROXI-GPIO-L: SIDE-L1.4; also elsewhere on the board
/MCU-STM32/SIDE-PROXI-GPIO-R: SIDE-R1.4; also elsewhere on the board
/MCU-STM32/USART2-IR-L-RX: SIDE-R1.3; also elsewhere on the board
/MCU-STM32/USART4-IR-R-RX: SIDE-L1.3; also elsewhere on the board
GND: SIDE-L1.2, SIDE-L1.8, SIDE-L1.9, SIDE-R1.2, SIDE-R1.8, SIDE-R1.9; also elsewhere on the board
VCC-3V3-P: SIDE-L1.1, SIDE-R1.1; also elsewhere on the board

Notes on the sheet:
SIDE PROXI IR SENSORs

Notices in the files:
README.md:
License: Apache-2.0
